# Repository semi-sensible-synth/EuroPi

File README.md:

# EuroPi (Semi-Sensible Synth THT KiCad remix)

This is a remix of the [original EuroPi](https://github.com/Allen-Synthesis/EuroPi) eurorack module with a few changes:

- Input jacks at bottom, above output jacks
- Uses cheaper (?) tactile buttons
- Uses a 38mm OLED, commonly sold on AliExpress

If you are building one right now ... [use the iBOM](https://rawcdn.githack.com/semi-sensible-synth/EuroPi/e1486020547788293de8dd8d0f69c1b8743ea925/hardware/EuroPi/kicad/ibom/ibom.html) to help with parts placement.

The EuroPi is a fully user reprogrammable module based on the [Raspberry Pi Pico](https://www.raspberrypi.com/products/raspberry-pi-pico/), which allows users to process inputs and controls to produce outputs based on code written in Python. The entire project is open-source.

<p>

</p>

---

This repository relates to the EuroPi module, however some users may be expecting to see what is now referred to as the 'EuroPi Prototype'. The repository for this (now deprecated) module [can be found here](https://github.com/roryjamesallen/EuroPi-Prototype)

You can find more about this and other projects of mine on [my website](https://www.allensynthesis.co.uk)

## Capabilities

* 6 0-10V Control Voltage outputs, each with indicator LED
* 2 Knobs with 12 bit resolution
* 2 Push Buttons
* 1 0-12V Control Voltage input with 12 bit resolution
* 1 Digital input for external clocking or gate sources
* 128x32 OLED Display
* I²C expansion header on the rear for extra sensors or outputs

### Documentation

**Hardware**: Details of the hardware can be found at [hardware README](hardware/EuroPi/README.md). Additionally the [BoM](hardware/EuroPi/bill_of_materials.md) and the [build guide](hardware/EuroPi/build_guide.md) can be found in the hardware folder.

**Software**: Before using any of the software, follow the instructions in [programming_instructions.md](software/programming_instructions.md) to set up and calibrate your module.

A list of user contributed scripts and their usage can be found in [contrib/README.md](software/contrib/README.md).
There is also a [YouTube playlist](https://www.youtube.com/playlist?list=PLbingtr9KGPUdIODLWgzgAdIyN497YyEs) showcasing EuroPi and some of the different scripts available.

The EuroPi firmware API documentation can be found at https://allen-synthesis.github.io/EuroPi/. This documentation will explain all of the available features of the EuroPi firmware API. It also includes some examples of how to use various features of the firmware as well as [interesting_things.md](software/interesting_things.md).

If you would like to extend any of the features of the EuroPi software, you can view the firmware source code at [europi.py](software/firmware/europi.py).

### Issues
If you find any bugs, either in the software, the hardware, or the documentation, please create an Issue by clicking the 'Issue' tab along the top.  
Please feel free to create any issue you see fit, I'll either attempt to fix it or explain it.  
There are Issue templates available, so please choose whichever is most relevant, depending on if your Issue is a hardware or software bug, if it's a documentation error or suggestion, if it's a question about the project as a whole, or a suggestion about the project as a whole.

### License

This module, and any documentation included in this repository, is entirely "free" software and hardware, under different licenses depending on the software, hardware, and documentation itself.

* Software: [Apache 2.0](software/LICENSE)
* Hardware: [CERN OHL-S v2](hardware/LICENSE)
* Documentation: [CC0 1.0](LICENSE)

Anyone is welcome to design their own versions of the idea, or modify my designs.
The only thing I would ask is that you refrain from using the brand name 'Allen Synthesis' on your DIY builds if they have modified my files in any way, just to prevent any confusion if they end up being re-sold or distributed. This is in line with section 8.2 of the CERN license. You may use the brand name if you have simply copied the files from this repository to replicate without modification.
  
If you have a bug fix or improvement that you think is worth sharing, then feel free to send over any pictures or documentation and it can be merged with the main project!
 
### Disclaimer
 
Recreate any of the files found in this repository at your own risk; I will attempt to solve any issues that you might have with my designs, but I can't guarantee that there are not minor bugs in any of the documents, both hardware and software.

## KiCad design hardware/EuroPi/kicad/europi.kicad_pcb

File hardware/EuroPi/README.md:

# EuroPi hardware (Semi-Sensible Synth THT KiCad remix)

This version of EuroPi is a remix with some small changes.

## Differences / changes from stock EuroPi

- Input jacks at bottom, above output jacks
- Uses 14mm high, 6x6mm base tactile buttons with ~6.1-6.2mm diameter plastic caps.
- Uses a 38mm OLED, commonly sold on AliExpress (mounted slightly offset from centre for your OCD)
- Has a bodge zone with some extra holes and exposed pads for cutting traces and re-routing the OLED pins if yours doesn’t follow the ‘CPC’-style pinout (less elegant than the original EuroPi rerouting holes, but intended as a last resort if you happen to have another OLED that still fits)
- Has optional non-electrical pin header to help support the other end of the OLED
- No standoff screw joining boards, extra pin headers at bottom instead
- General re-routing and component position tweaks to make it all work.

## BOM variations of note

- 0.91” OLED (38mm wide, GND/VCC/SCL/SDA): [Ali Express](https://www.aliexpress.com/item/32672229793.html)
- 6x6x14 mm tactile buttons: [Ali Express](https://www.aliexpress.com/item/32960657626.html)
- Tactile button caps: [Ali Express (white)](https://www.aliexpress.com/item/32872180785.html), [Ali Express (black)](https://www.aliexpress.com/item/32873394381.html)

These are common parts across various sellers, so should be relatively easy to find at a good price.

## v0.10.0-sss-tht TODO notes

I have ordered and built a module using the `v0.10.0-sss-tht` production files and it works.
These are some minor changes I would make in a revision.

- Add more component value labels to silkscreen, especially to resistors
- Add + to LED silkscreen
- LED panel holes could be a little smaller (~0.4mm diameter smaller)
- Consider adding pin headers between the front panel and PCB, above the OLED to better secure when using nut-less trimmer pots.
  - _(This would be a female header above the OLED and an SMD right angle male header on exposed pads on the back of the front panel - or get fancy with a solderable standoff like https://www.adafruit.com/product/4207)_
- Build guide: 
  - Solder the I2C header before Pico & power header (tricky otherwise)
  - Solder the bottom centre jack (J5) before bottom board joiner on the opposite side of the board (if using 8x1 with two middle pins removed as joiner). If you forget, it can be soldered from the opposite side of the board.
  - I had to glue my button caps on to the tactile buttons - not a big deal, but I expected them to attach via friction
  - I used small plastic trimmer pots in my first build, however it’s better to use proper metal pots with nuts. This is because without pot nuts, pressing the buttons too hard flexes the PCB away from the front panel. Using [trimmer knobs](https://www.aliexpress.com/item/1005002336855641.html) also help.

# Hardware Specifications

## Outputs
- 1k Output Impedance
- RC filter smoothed PWM
- ~1.5kHz Maximum usable frequency (without changing RC values)
- 0.000176V Maximum ripple peak-to-peak
- 0.0108s Settle time from 0% to 90% duty cycle
- 0-10V

## Analogue Input
- 100k Input Impedance
- 0-12V Readable Range
- Protected for ±36V (TL074 limits, MCP6002 will always clip to ±3.3V)

## Digital Input
- 100k Input Impedance
- 0.8V threshold to read as high

## OLED
- SSD1306 0.91"
- 128 x 32 pixels
- I2C Protocol

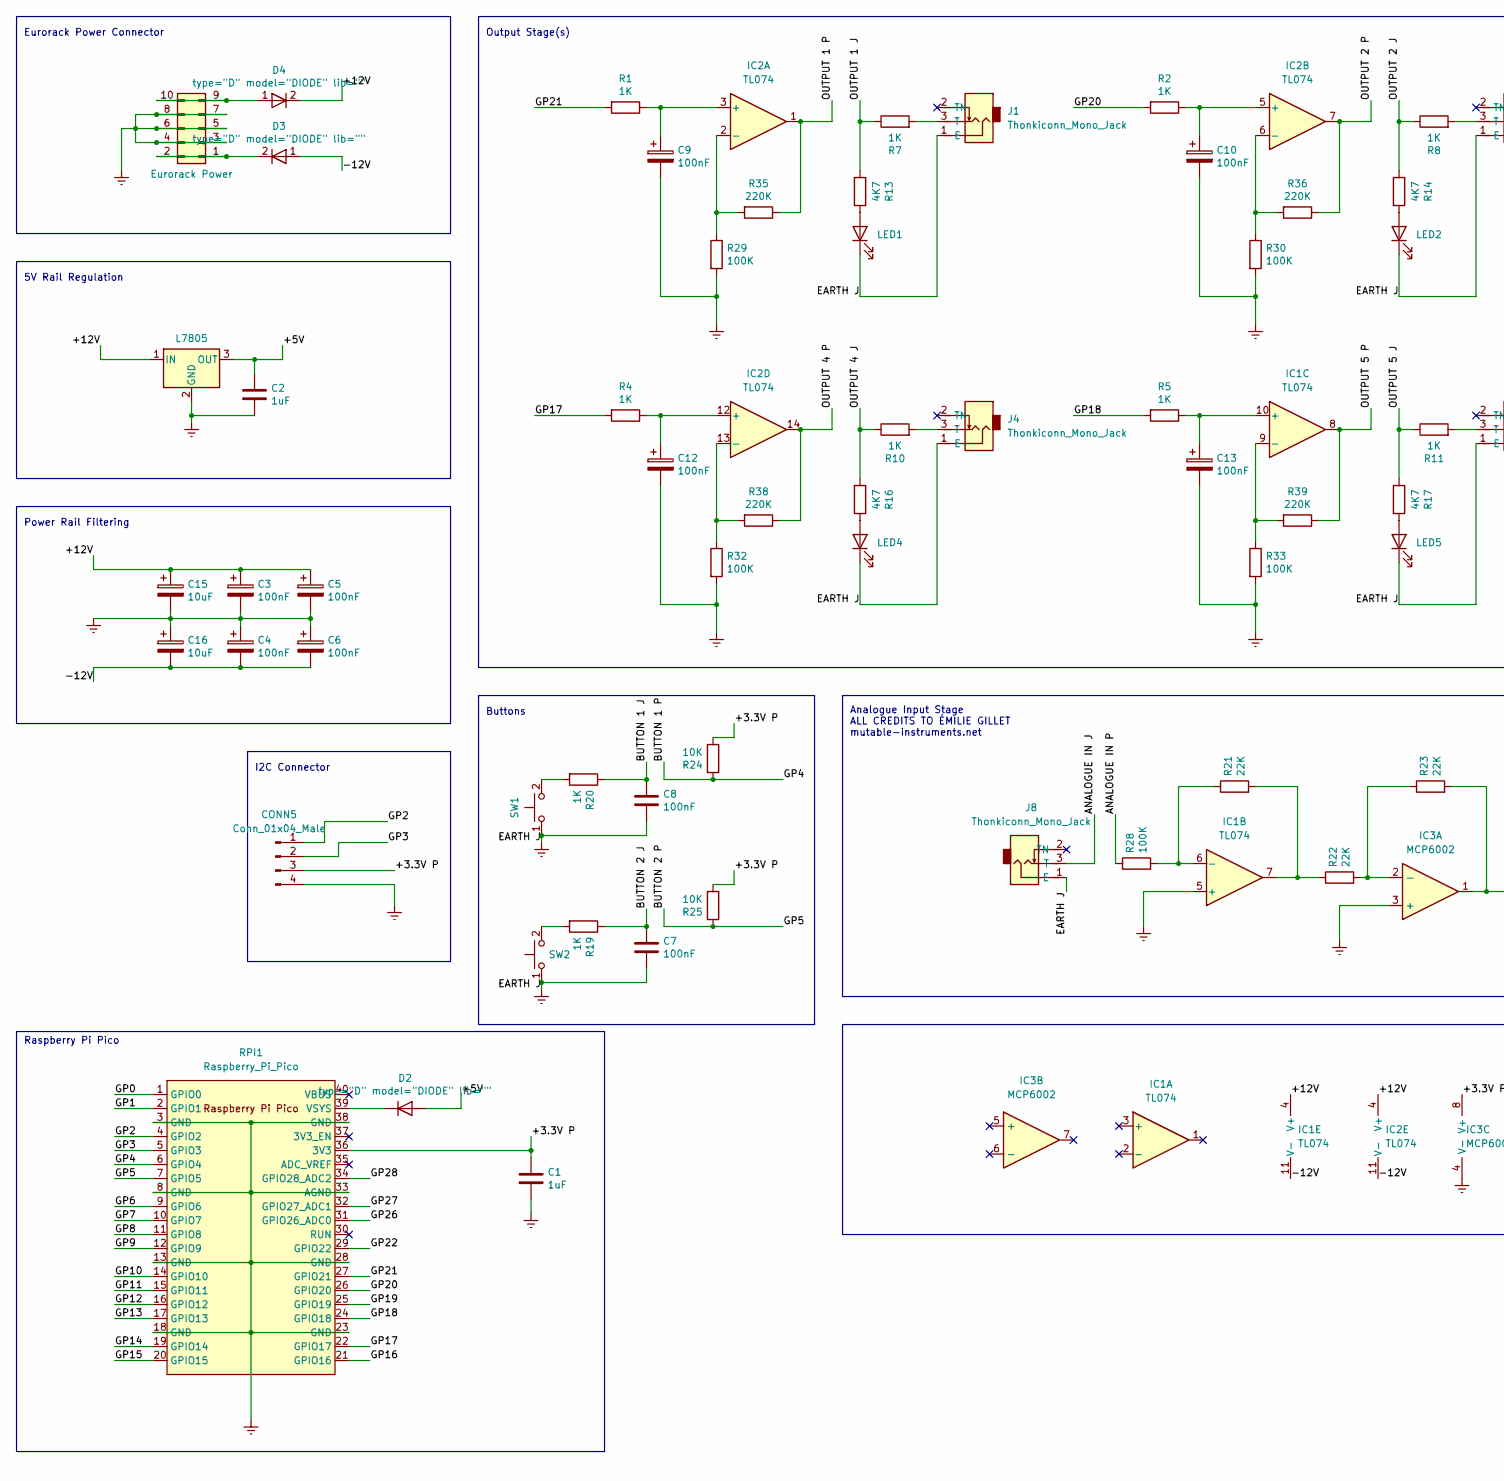
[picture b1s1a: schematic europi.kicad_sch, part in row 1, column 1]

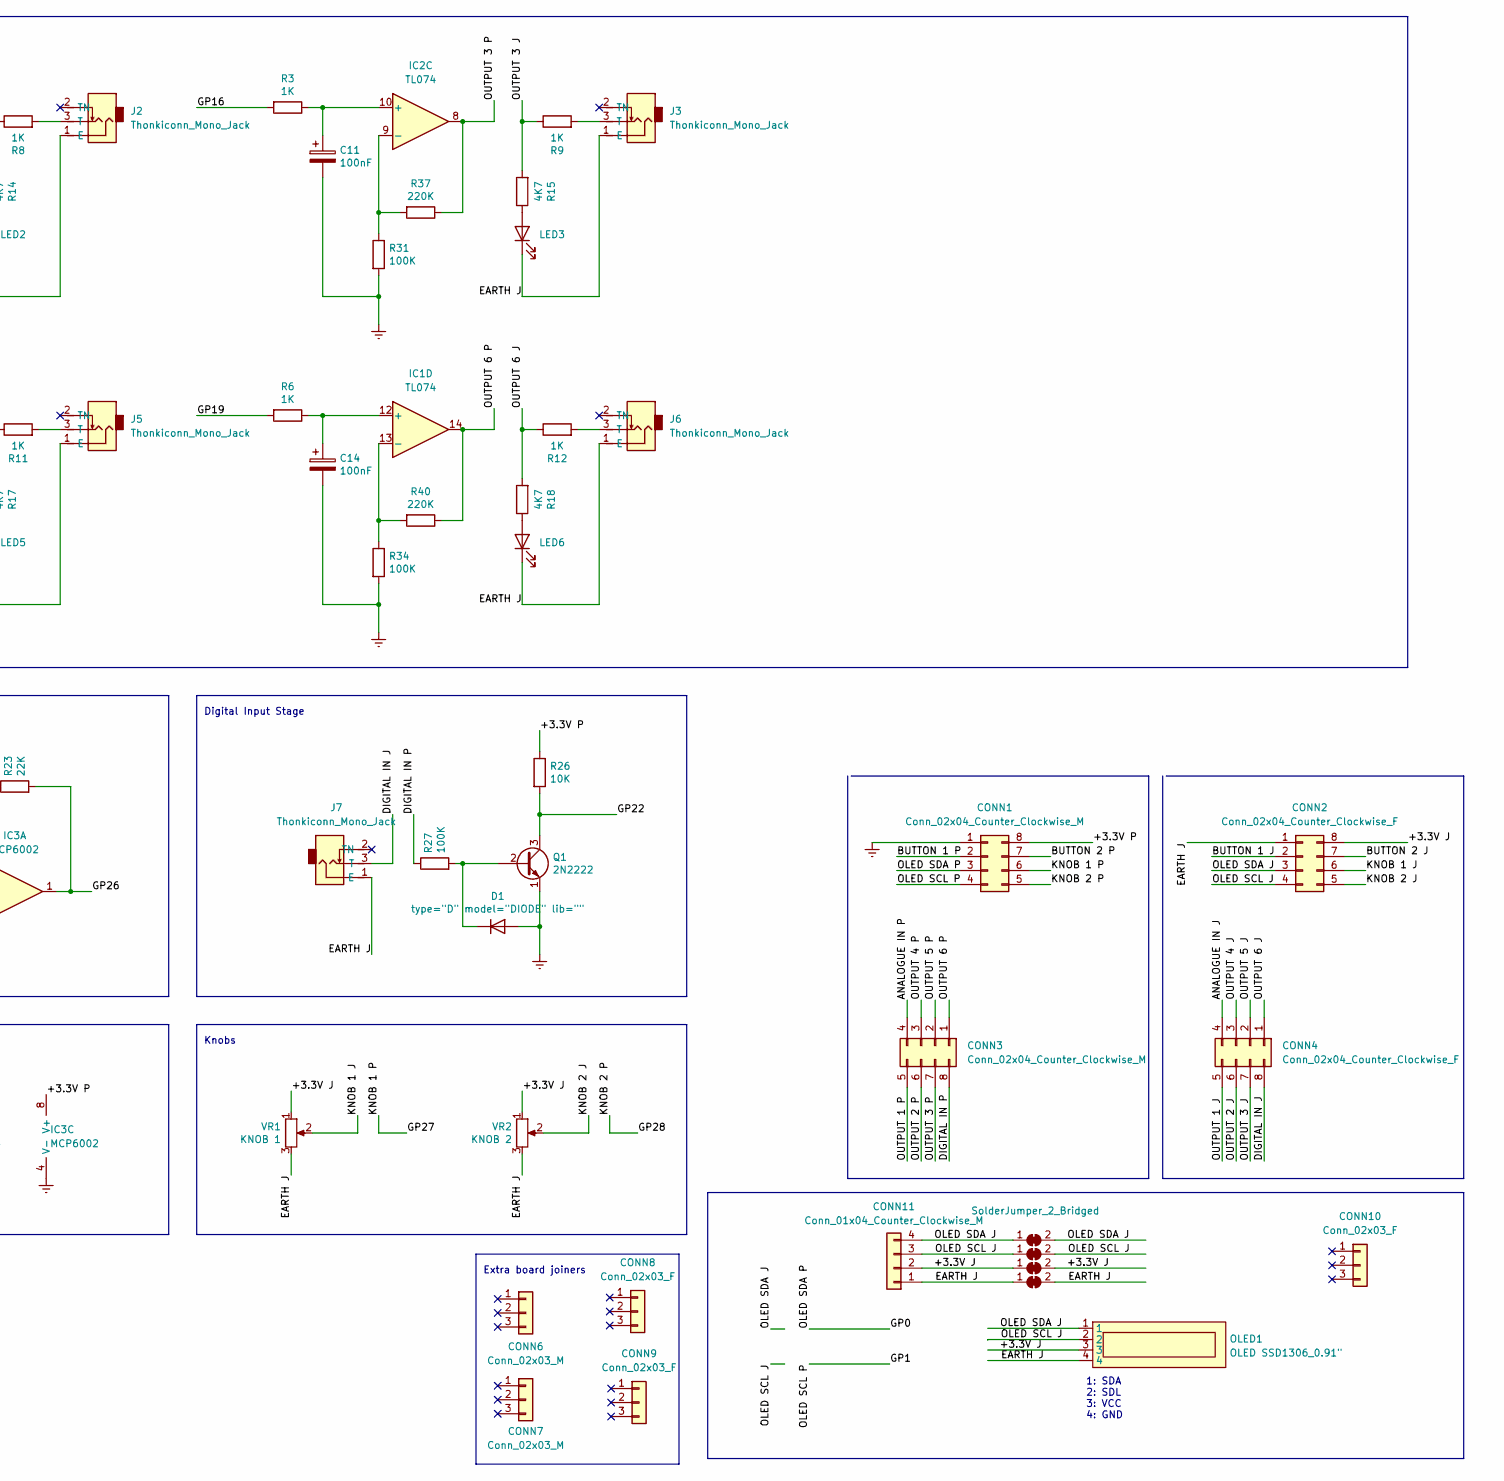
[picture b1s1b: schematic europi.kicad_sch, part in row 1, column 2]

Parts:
C1, C2: 1uF; CP_Radial_D5.0mm_P2.50mm
C3, C4, C5, C6, C7, C8, C9, C10, C11, C12, C13, C14: 100nF; Capacitor Small Non-Polarised
C15, C16: 10uF; CP_Radial_D8.0mm_P3.80mm
CONN1, CONN3: Conn_02x04_Counter_Clockwise_M; PinHeader_2x04_P2.54mm_Vertical
CONN2, CONN4: Conn_02x04_Counter_Clockwise_F; PinSocket_2x04_P2.54mm_Vertical
CONN5: Conn_01x04_Male; PinHeader_1x04_P2.54mm_Vertical
CONN6, CONN7: Conn_02x03_M; PinHeader_1x03_P2.54mm_Vertical
CONN8, CONN9, CONN10: Conn_02x03_F; PinSocket_1x03_P2.54mm_Vertical
CONN11: Conn_01x04_Counter_Clockwise_M; PinHeader_1x04_P2.54mm_Vertical
D1, D2, D3, D4: type="D" model="DIODE" lib=""; Schottky Diode
EuroPower1: Eurorack Power; Eurorack Power Header Unlabeled
IC1, IC2: TL074; DIP-14 IC Socket
IC3: MCP6002; DIP-8 IC Socket
J1, J2, J3, J4, J5, J6, J7, J8: Thonkiconn_Mono_Jack; Thonkiconn Mono Jack
JP1, JP2, JP3, JP4: SolderJumper_2_Bridged; SolderJumper-2_P1.3mm_Bridged_Pad1.0x1.5mm
LED1, LED2, LED3, LED4, LED5, LED6: LED; LED 3mm
OLED1: OLED SSD1306_0.91"; OLED SSD1306 0.91-38mm
Q1: 2N2222; TO-92
R1, R2, R3, R4, R5, R6, R7, R8, R9, R10, R11, R12, R19, R20: 1K; R_Axial_DIN0204_L3.6mm_D1.6mm_P7.62mm_Horizontal
R13, R14, R15, R16, R17, R18: 4K7; R_Axial_DIN0204_L3.6mm_D1.6mm_P7.62mm_Horizontal
R21, R22, R23: 22K; R_Axial_DIN0204_L3.6mm_D1.6mm_P7.62mm_Horizontal
R24, R25, R26: 10K; R_Axial_DIN0204_L3.6mm_D1.6mm_P7.62mm_Horizontal
R27, R28, R29, R30, R31, R32, R33, R34: 100K; R_Axial_DIN0204_L3.6mm_D1.6mm_P7.62mm_Horizontal
R35, R36, R37, R38, R39, R40: 220K; R_Axial_DIN0204_L3.6mm_D1.6mm_P7.62mm_Horizontal
REG1: L7805; TO-220-3_Vertical
RPI1: Raspberry_Pi_Pico; Raspberry Pi Pico
SW1, SW2: SW_Push; SW_PUSH_6mm
VR1: KNOB 1; Potentiometer_RV09
VR2: KNOB 2; Potentiometer_RV09

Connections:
/+3.3V J: CONN2.8, CONN11.2, JP3.1 (A), JP3.2 (B), OLED1.3, VR1.1, VR2.1
/+3.3V P: C1.1, CONN1.8, CONN5.3, IC3.8 (V+), R24.2, R25.2, R26.1, RPI1.36 (3V3)
/+5V: C2.1, D2.1 (A), REG1.3 (OUT)
/+12V: C3.1, C5.1, C15.1, D4.2 (K), IC1.4 (V+), IC2.4 (V+), REG1.1 (IN)
/-12V: C4.2, C6.2, C16.2, D3.1 (A), IC1.11 (V-), IC2.11 (V-)
/ANALOGUE IN J: CONN4.4, J8.3 (T)
/ANALOGUE IN P: CONN3.4, R28.1
/BUTTON 1 J: C8.1, CONN2.2, R20.1
/BUTTON 1 P: CONN1.2, R24.1, RPI1.6 (GPIO4)
/BUTTON 2 J: C7.1, CONN2.7, R19.1
/BUTTON 2 P: CONN1.7, R25.1, RPI1.7 (GPIO5)
/DIGITAL IN J: CONN4.8, J7.3 (T)
/DIGITAL IN P: CONN3.8, R27.1
/GP0: CONN1.3, RPI1.1 (GPIO0)
/GP1: CONN1.4, RPI1.2 (GPIO1)
/GP2: CONN5.1, RPI1.4 (GPIO2)
/GP3: CONN5.2, RPI1.5 (GPIO3)
/GP6: RPI1.9 (GPIO6)
/GP7: RPI1.10 (GPIO7)
/GP8: RPI1.11 (GPIO8)
/GP9: RPI1.12 (GPIO9)
/GP10: RPI1.14 (GPIO10)
/GP11: RPI1.15 (GPIO11)
/GP12: RPI1.16 (GPIO12)
/GP13: RPI1.17 (GPIO13)
/GP14: RPI1.19 (GPIO14)
/GP15: RPI1.20 (GPIO15)
/GP16: R3.2, RPI1.21 (GPIO16)
/GP17: R4.2, RPI1.22 (GPIO17)
/GP18: R5.2, RPI1.24 (GPIO18)
/GP19: R6.2, RPI1.25 (GPIO19)
/GP20: R2.2, RPI1.26 (GPIO20)
/GP21: R1.2, RPI1.27 (GPIO21)
/GP22: Q1.3 (C), R26.2, RPI1.29 (GPIO22)
/GP26: IC3.1, R23.2, RPI1.31 (GPIO26_ADC0)
/GP27: CONN1.6, RPI1.32 (GPIO27_ADC1)
/GP28: CONN1.5, RPI1.34 (GPIO28_ADC2)
/KNOB 1 J: CONN2.6, VR1.2
/KNOB 2 J: CONN2.5, VR2.2
/OLED SCL J: CONN2.4, CONN11.3, JP2.1 (A), JP2.2 (B), OLED1.2
/OLED SDA J: CONN2.3, CONN11.4, JP1.1 (A), JP1.2 (B), OLED1.1
/OUTPUT 1 J: CONN4.5, R7.1, R13.2
/OUTPUT 1 P: CONN3.5, IC2.1, R35.1
/OUTPUT 2 J: CONN4.6, R8.1, R14.2
/OUTPUT 2 P: CONN3.6, IC2.7, R36.1
/OUTPUT 3 J: CONN4.7, R9.1, R15.2
/OUTPUT 3 P: CONN3.7, IC2.8, R37.1
/OUTPUT 4 J: CONN4.3, R10.1, R16.2
/OUTPUT 4 P: CONN3.3, IC2.14, R38.1
/OUTPUT 5 J: CONN4.2, R11.1, R17.2
/OUTPUT 5 P: CONN3.2, IC1.8, R39.1
/OUTPUT 6 J: CONN4.1, R12.1, R18.2
/OUTPUT 6 P: CONN3.1, IC1.14, R40.1
Earth: C1.2, C2.2, C3.2, C4.1, C5.2, C6.1, C7.2, C8.2, C9.2, C10.2, C11.2, C12.2, C13.2, C14.2, C15.2, C16.1, CONN1.1, CONN2.1, CONN5.4, CONN11.1, D1.1 (A), EuroPower1.3, EuroPower1.4, EuroPower1.5, EuroPower1.6, EuroPower1.7, EuroPower1.8, IC1.5 (+), IC3.3 (+), IC3.4 (V-), J1.1 (E), J2.1 (E), J3.1 (E), J4.1 (E), J5.1 (E), J6.1 (E), J7.1 (E), J8.1 (E), JP4.1 (A), JP4.2 (B), LED1.1 (K), LED2.1 (K), LED3.1 (K), LED4.1 (K), LED5.1 (K), LED6.1 (K), OLED1.4, Q1.1 (E), R29.2, R30.2, R31.2, R32.2, R33.2, R34.2, REG1.2 (GND), RPI1.3 (GND), RPI1.8 (GND), RPI1.13 (GND), RPI1.18 (GND), RPI1.23 (GND), RPI1.28 (GND), RPI1.33 (AGND), RPI1.38 (GND), SW1.1, SW2.1, VR1.3, VR2.3
unnamed: D1.2 (K), Q1.2 (B), R27.2
unnamed: D2.2 (K), RPI1.39 (VSYS)
unnamed: D3.2 (K), EuroPower1.1, EuroPower1.2
unnamed: D4.1 (A), EuroPower1.9, EuroPower1.10
unnamed: IC1.7, R21.2, R22.1
unnamed: IC1.6 (-), R21.1, R28.2
unnamed: C13.1, IC1.10 (+), R5.1
unnamed: IC1.9 (-), R33.1, R39.2
unnamed: C14.1, IC1.12 (+), R6.1
unnamed: IC1.13 (-), R34.1, R40.2
unnamed: C9.1, IC2.3 (+), R1.1
unnamed: IC2.2 (-), R29.1, R35.2
unnamed: C10.1, IC2.5 (+), R2.1
unnamed: IC2.6 (-), R30.1, R36.2
unnamed: C11.1, IC2.10 (+), R3.1
unnamed: IC2.9 (-), R31.1, R37.2
unnamed: C12.1, IC2.12 (+), R4.1
unnamed: IC2.13 (-), R32.1, R38.2
unnamed: IC3.2 (-), R22.2, R23.1
unnamed: J1.3 (T), R7.2
unnamed: J2.3 (T), R8.2
unnamed: J3.3 (T), R9.2
unnamed: J4.3 (T), R10.2
unnamed: J5.3 (T), R11.2
unnamed: J6.3 (T), R12.2
unnamed: LED1.2 (A), R13.1
unnamed: LED2.2 (A), R14.1
unnamed: LED3.2 (A), R15.1
unnamed: LED4.2 (A), R16.1
unnamed: LED5.2 (A), R17.1
unnamed: LED6.2 (A), R18.1
unnamed: R19.2, SW2.2
unnamed: R20.2, SW1.2

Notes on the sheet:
Buttons
5V Rail Regulation
Analogue Input Stage ALL CREDITS TO ÉMILIE GILLET mutable-instruments.net
Power Rail Filtering
Eurorack Power Connector
I2C Connector
Digital Input Stage
Extra board joiners
Raspberry Pi Pico
Output Stage(s)
1: SDA 2: SDL 3: VCC 4: GND
Knobs

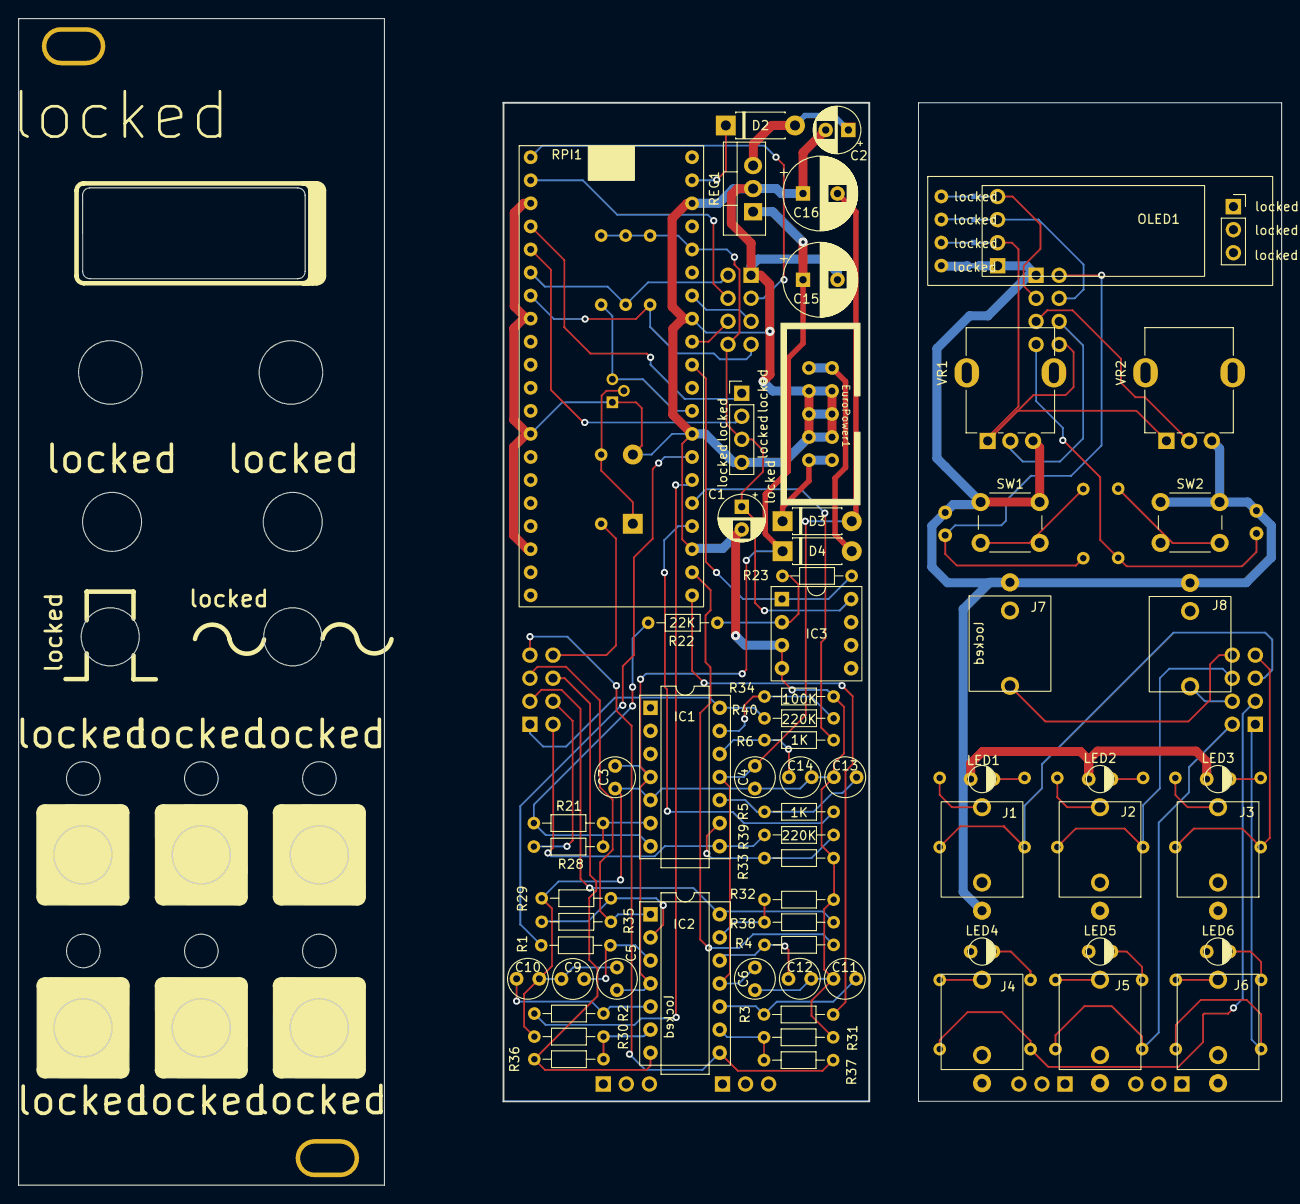
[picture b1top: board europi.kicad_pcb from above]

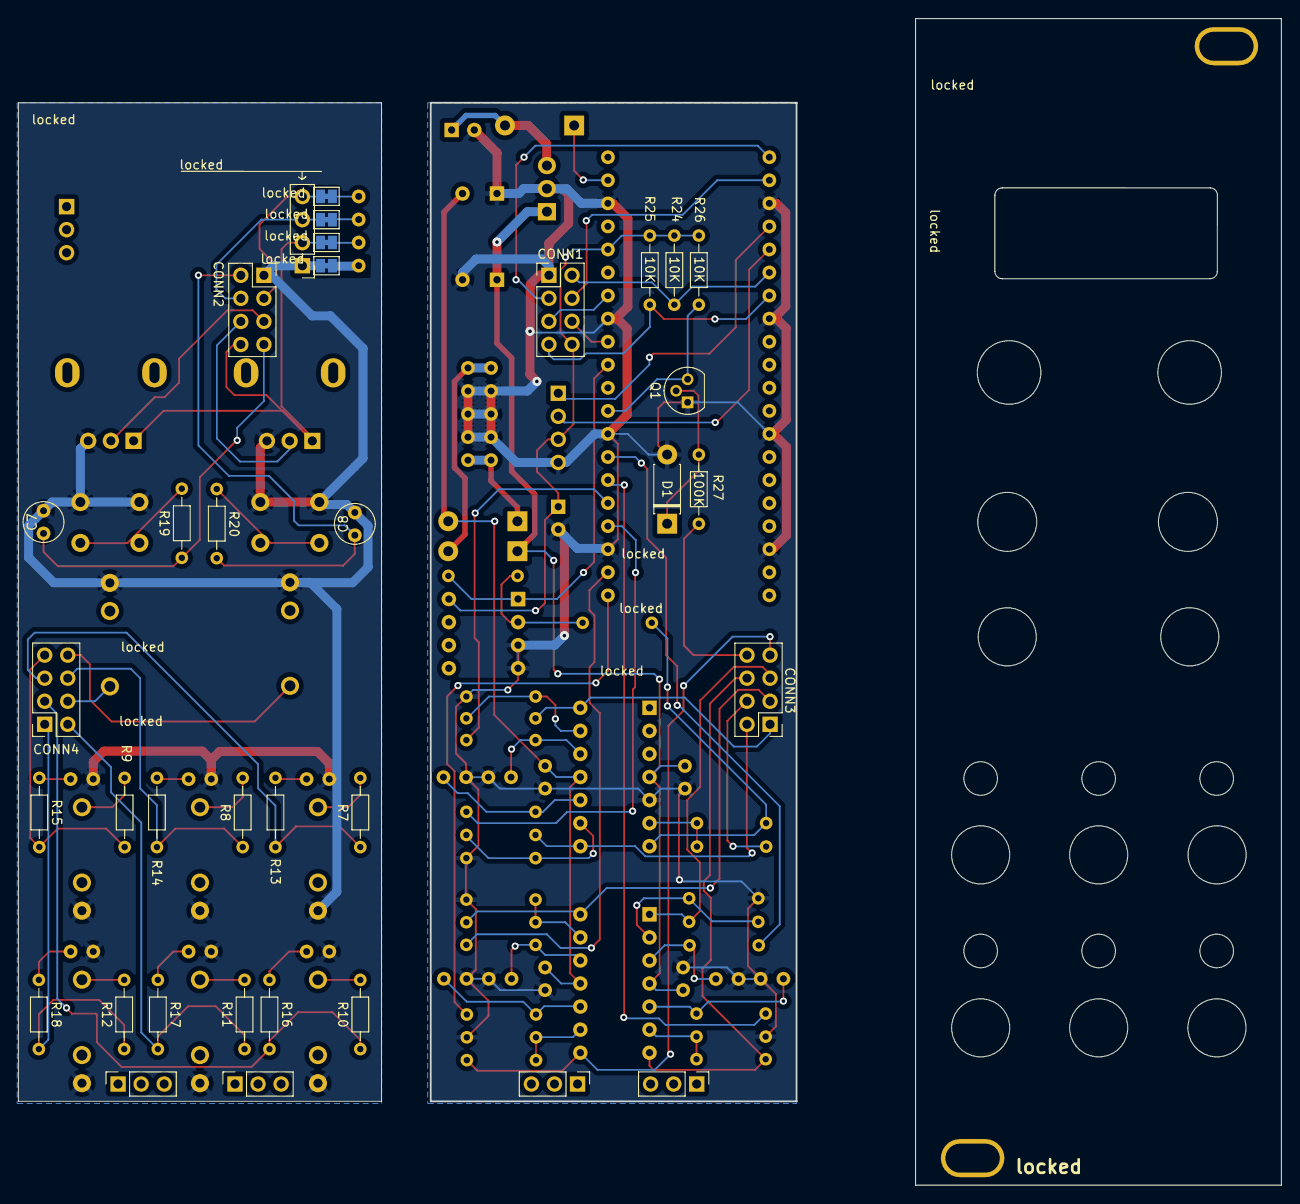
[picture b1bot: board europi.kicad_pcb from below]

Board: 2 copper layers, 139.0 x 128.4 mm, 109 parts (35 on the bottom side), 77 nets.

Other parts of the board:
3.7mm LED hole, 3.7mm LED hole#2, 3.7mm LED hole#3, 3.7mm LED hole#4, 3.7mm LED hole#5, 3.7mm LED hole#6: MountingHole_3.7mm
M3_MOUNT_BOTTOM, M3_MOUNT_TOP: MountingHole_M3

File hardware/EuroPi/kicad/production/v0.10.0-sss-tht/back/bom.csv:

Designator,Footprint,Quantity,Value,LCSC Part #
"C1, C2",CP_Radial_D5.0mm_P2.50mm,2,1uF,
"C10, C11, C12, C13, C14, C3, C4, C5, C6, C9",Capacitor Small Non-Polarised,10,100nF,
"C15, C16",CP_Radial_D8.0mm_P3.80mm,2,10uF,
"CONN1, CONN3",PinHeader_2x04_P2.54mm_Vertical,2,Conn_02x04_Counter_Clockwise_M,
CONN5,PinHeader_1x04_P2.54mm_Vertical,1,Conn_01x04_Male,
"CONN6, CONN7",PinHeader_1x03_P2.54mm_Vertical,2,Conn_02x03_M,
"D1, D2, D3, D4",Schottky Diode,4,"type=""D"" model=""DIODE"" lib=""""",
EuroPower1,Eurorack Power Header Unlabeled,1,Eurorack Power,
"IC1, IC2",DIP-14 IC Socket,2,TL074,
IC3,DIP-8 IC Socket,1,MCP6002,
Q1,TO-92,1,2N2222,
"R1, R2, R3, R4, R5, R6",R_Axial_DIN0204_L3.6mm_D1.6mm_P7.62mm_Horizontal,6,1K,
"R21, R22, R23",R_Axial_DIN0204_L3.6mm_D1.6mm_P7.62mm_Horizontal,3,22K,
"R24, R25, R26",R_Axial_DIN0204_L3.6mm_D1.6mm_P7.62mm_Horizontal,3,10K,
"R27, R28, R29, R30, R31, R32, R33, R34",R_Axial_DIN0204_L3.6mm_D1.6mm_P7.62mm_Horizontal,8,100K,
"R35, R36, R37, R38, R39, R40",R_Axial_DIN0204_L3.6mm_D1.6mm_P7.62mm_Horizontal,6,220K,
REG1,TO-220-3_Vertical,1,L7805,
RPI1,Raspberry Pi Pico,1,Raspberry_Pi_Pico,

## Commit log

2023-10-22 KiCad redesign with all jacks on bottom, 38mm OLED
2023-10-22 Remix v0.10.0-sss-tht production files
2023-10-22 Add ibom for remix
2023-10-22 Fix OLED window offset, add OLED I2C labels
2023-10-22 Update docs to reflect sss-tht remix
2023-10-22 New image in README.md
2023-10-22 Add OLED dimensions image to bom
2023-11-13 Update README.md
    Add viewable link to iBOM from README.

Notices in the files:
hardware/EuroPi/kicad/europi.kicad_sch:
CC BY-SA 3.0
